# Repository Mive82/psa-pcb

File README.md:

# Important

**NOTE:** Unless you have access to a bunch of weird ICs used here, a way to solder 0201 and 0402 components,
and willpower to fix the defects listed below, don't bother assemblying the v1.0 version of the PCB.

# Peugeot Infotainment Project PCB

This is a repository for the PCB used in the second revision of the Peugeot Infotainment Project.
For the first revision, see the v0.1 branch.

It used <https://github.com/morcibacsi/PSAVanCanBridgeHW> as a base for the VAN communication hardware.

For more information, check out <https://github.com/Mive82/psa-docs>

## About the board

Unlike the previous v0.1 revision, on the v1.0 revision everything is contained on the board:
- Dual buck converter chips: One for the ESP and other ICs on the board (Battery power) and one for the Raspberry Pi and display (VAN+).
  - 3.3V LDO for the ESP32 after the 5V buck converter. Allows for very low voltage on the 12V input down to about 4 volts and the ESP will still work.
- ESP32-WROOM module. The USB to UART converter is not inclued, but the extra pins for resetting and flashing the board are routed to the connector.
- TSS463C VAN driver. Connected with a level shifter to the ESP
- MCP2551 CAN transciever. The RX pin is also connected to the ESP to allow receving in software.
- DS3231 RTC Chip for keeping the time. Connected to the Pi.

## Connections

The board has three JST GH connectors:
- Car power and data (JST GH 6 pin)
  - 12V battery power
  - 12V Switched (+VAN) power
  - VAN DATA and DATAB lines
- Display power output (JST GH 4 pin)
  - Outputs 5V for an external display
  - Also routes I2C pins from the Pi if needed
- ESP programming (JST GH 6 pin)
  - UART TX, RX, RTS and DTR pins as well as GND.

# Board Defects

Being the first proper revision, there are a lot of defects. Luckily they can all be solved.

## ESP flashing issues

The `GPIO12` pin is used for SPI communication with the TSS463C. It is also used as a strapping pin for determining the voltage used
to access the onboard flash. This pin is floating, so the value will not always be correct. This will result in regular booting
and flashing issues.

**SOLUTION**: Burn eFuses with `esptool.py` to permanently set the voltage used. On the ESP32-WROOM module we used, the voltage was 3.3V [Implemented]

## ESP first boot issues

When first powering the board on, the ESP will always boot into flash mode. This is because of a capacitor on the `GPIO0` pin that was not needed: `C6`.

**SOLUTION**: Remove the `C6` capacitor. [Implemented]

## VAN TX not working

The transistor switches used for putting the MCP2551 in a low-power state and resetting the TSS are not designed correctly.
They don't reset the TSS, but the MCP2551 is always put in a low power state which prevents it from sending any CAN/VAN data.

**SOLUTION**: Remove both transistor switches and surrounding hardware (`Q6`, `R21`, `R1`, `Q5` and `C1`). [Implemented]
Pull pin `Rs` on the MCP2551 to GND with a 4.7k resistor. Note that, according the datasheet, this will increase power draw
by 9 or 10 mA. [Implemented]

## ESP32 VAN RX not working after VAN+ dissapears

This issue occured due to an oversight on level shifter pins. The VCC reference pin on one side is tied to the VAN+ regulator and will
dissapear when VAN+ dissapears.

**SOLUTION**: On chip U11 cut the trace connecting pin 11 (`VCC(B)`) and `+5V ignition`. then connect pin 11 to `+5V Car Battery`. [Implemented]
Best location would the one of the pads of `R21` which is be removed to fix the issue above this one. 

### High deep sleep power consumption

The board pulls about 35mA on 12V during deep sleep. This increases the more voltage increases.
Not yet sure what is causing this, but removing the pull resistors from the `MODE` pins on the buck regulators reduces it to about 12mA.

**PARTIAL SOLUTION**: Remove `R110` and `R118`. [Implemented]

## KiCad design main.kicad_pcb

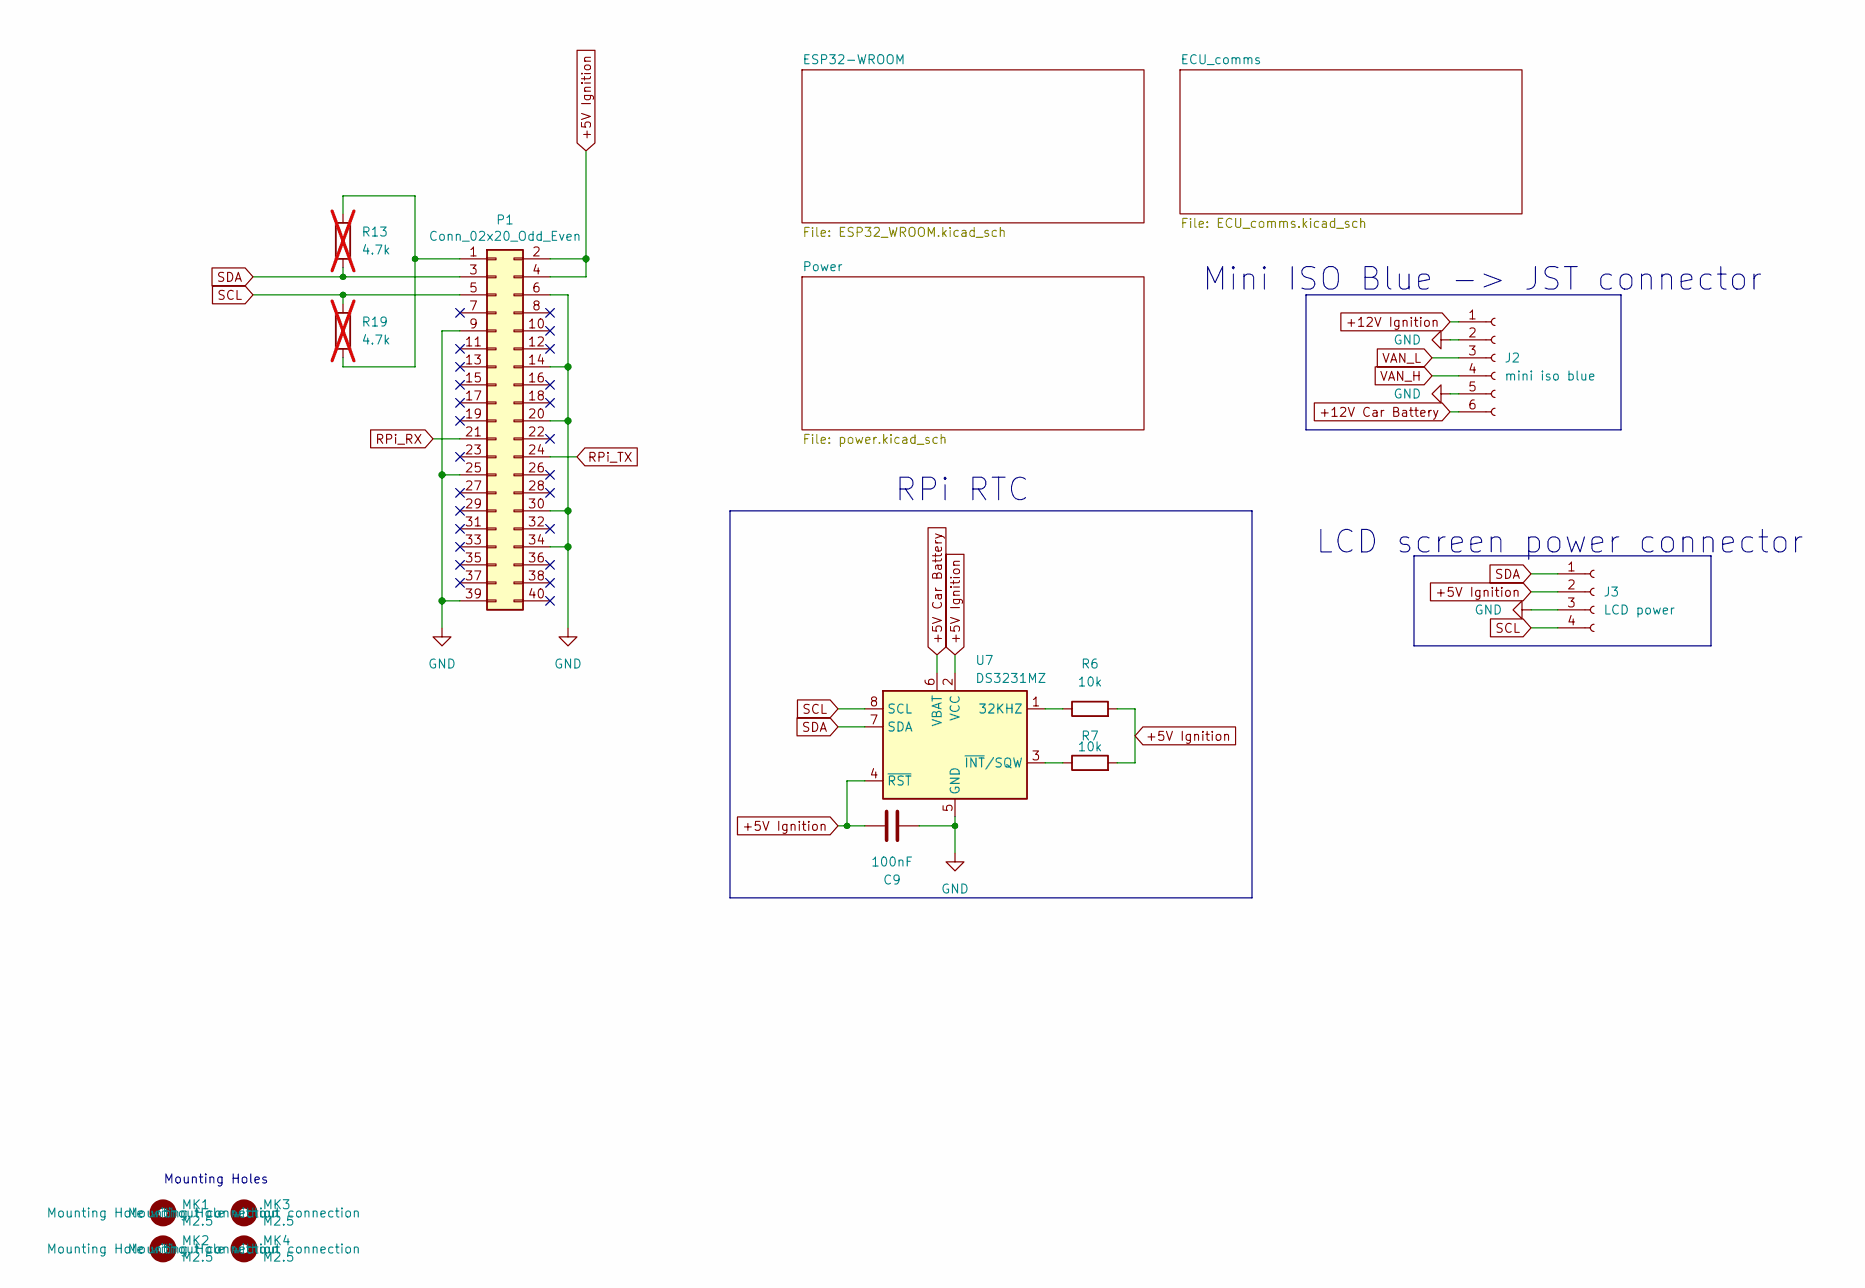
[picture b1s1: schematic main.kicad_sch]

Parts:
C9: 100nF; R_0805_2012Metric
J2: mini iso blue; JST_GH_SM06B-GHS-TB_1x06-1MP_P1.25mm_Horizontal
J3: LCD power; JST_GH_SM04B-GHS-TB_1x04-1MP_P1.25mm_Horizontal
MK1, MK2, MK3, MK4: M2.5; MountingHole_2.7mm_M2.5
P1: Conn_02x20_Odd_Even; PinSocket_2x20_P2.54mm_Vertical
R6, R7: 10k; R_0805_2012Metric
R13, R19: 4.7k; R_0402_1005Metric_Pad0.72x0.64mm_HandSolder; not fitted
U7: DS3231MZ; SOIC-8_3.9x4.9mm_P1.27mm

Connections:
+5V Car Battery: U7.6 (VBAT); also elsewhere on the board
+5V Ignition: C9.2, J3.2, P1.2, P1.4, R6.2, R7.2, U7.2 (VCC), U7.4 (~RST); also elsewhere on the board
+12V Car Battery: J2.6; also elsewhere on the board
+12V Ignition: J2.1; also elsewhere on the board
GND: C9.1, J2.2, J2.5, J3.3, P1.6, P1.9, P1.14, P1.20, P1.25, P1.30, P1.34, P1.39, U7.5 (GND); also elsewhere on the board
unnamed: P1.1, R13.1, R19.2
unnamed: R6.1, U7.1 (32KHZ)
unnamed: R7.1, U7.3 (~INT/SQW)
RPi_RX: P1.21; also elsewhere on the board
RPi_TX: P1.24; also elsewhere on the board
SCL: J3.4, P1.5, R19.1, U7.8 (SCL)
SDA: J3.1, P1.3, R13.2, U7.7 (SDA)
VAN_H: J2.4; also elsewhere on the board
VAN_L: J2.3; also elsewhere on the board

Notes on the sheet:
LCD screen power connector
Mini ISO Blue -> JST connector
Mounting Holes
RPi RTC

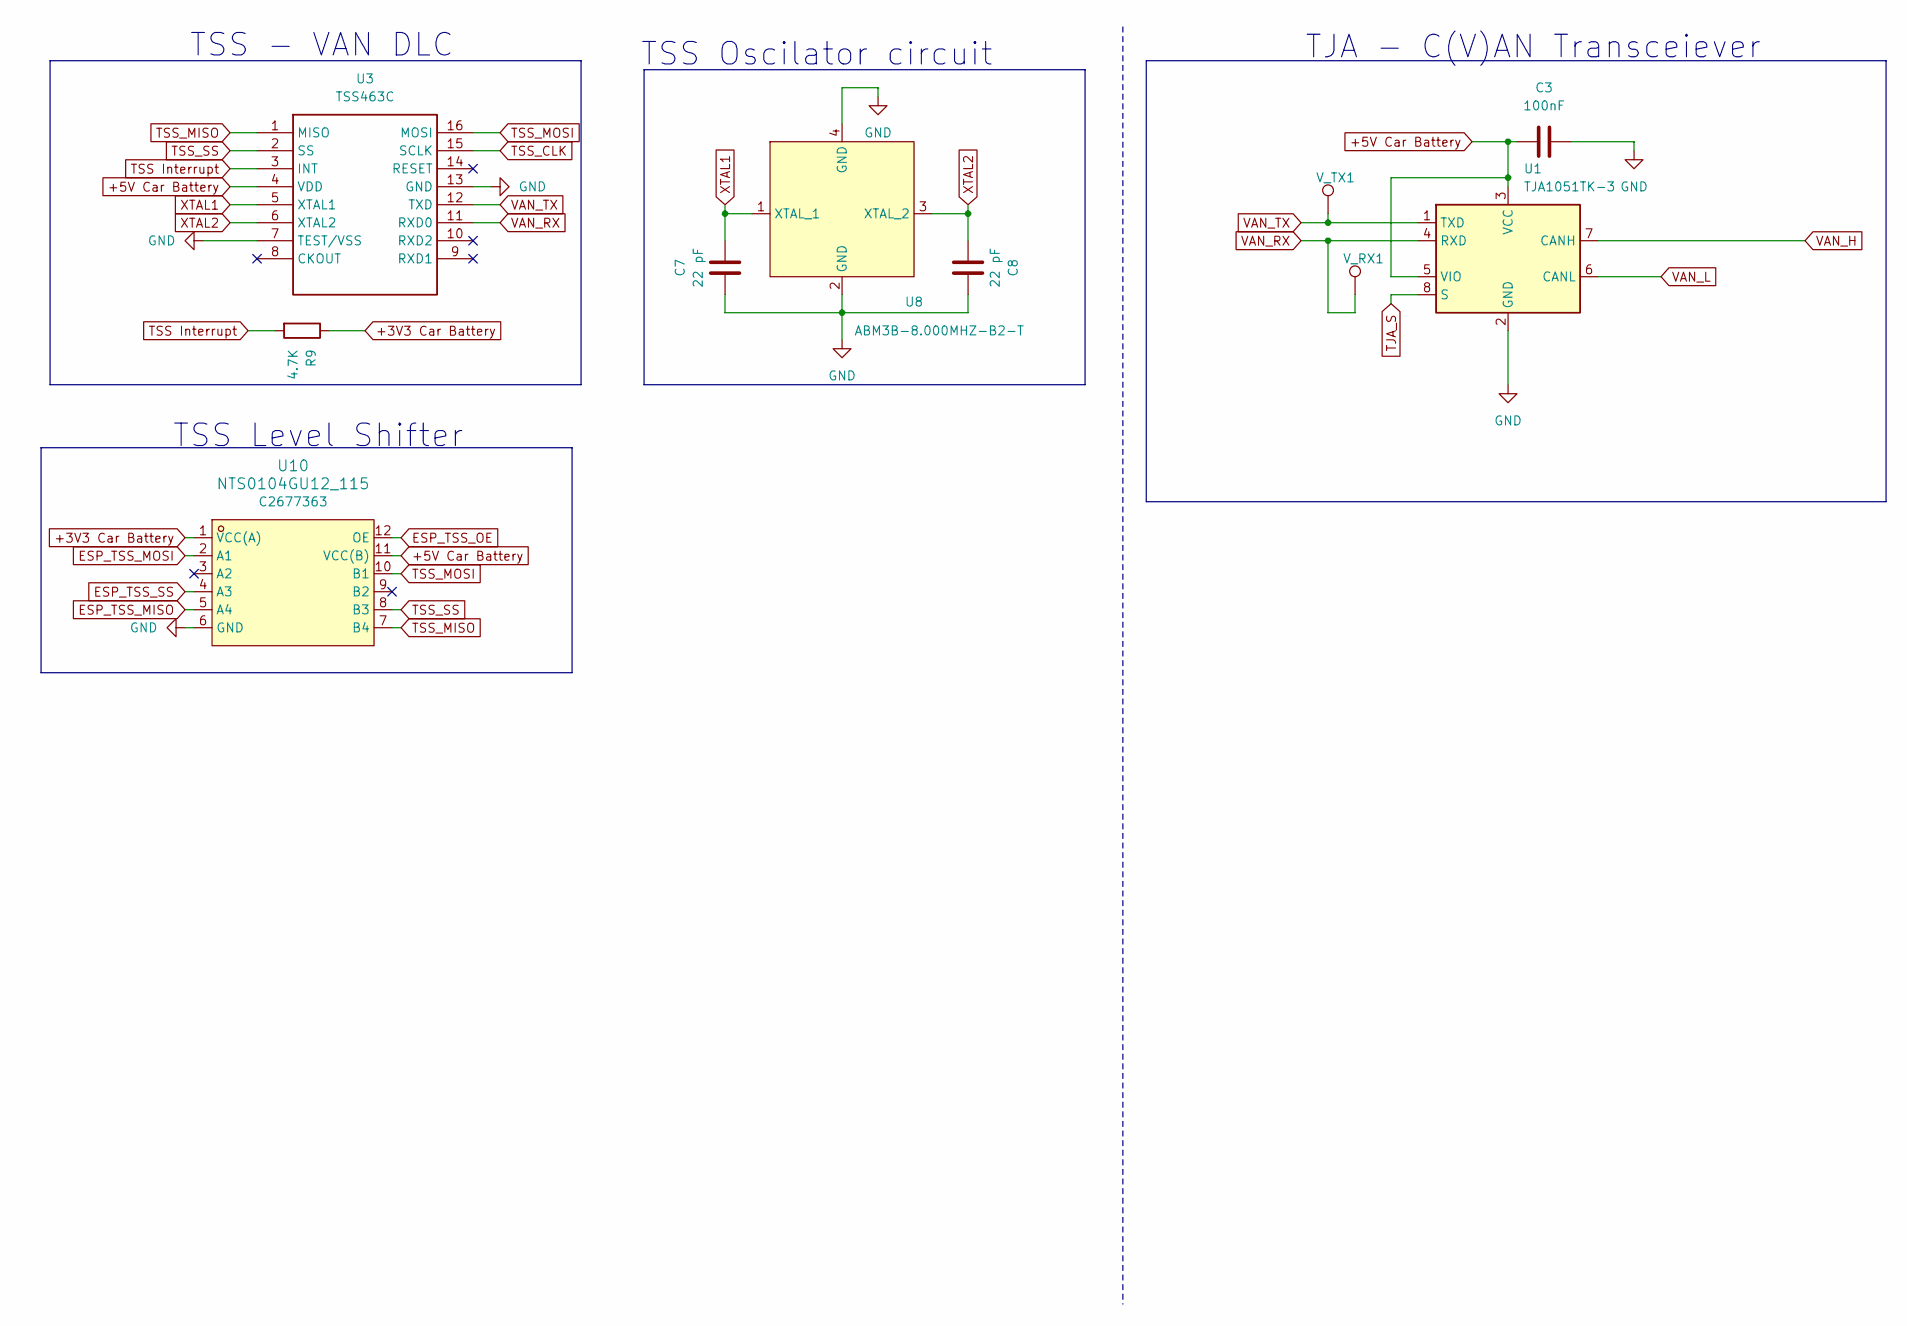
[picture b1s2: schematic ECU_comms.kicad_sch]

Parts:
C3: 100nF; C_0805_2012Metric
C7, C8: 22 pF; C_0805_2012Metric
R9: 4.7K; R_0805_2012Metric
U1: TJA1051TK-3; HVSON-8-1EP_3x3mm_P0.65mm_EP1.6x2.4mm
U3: TSS463C
U8: ABM3B-8.000MHZ-B2-T; Crystal_SMD_Abracon_ABM3B-4Pin_5.0x3.2mm
U10: NTS0104GU12_115; XQFN-12_L2.0-W1.7-P0.40-BL; LCSC Part C2677363
V_RX1: TestPoint; TestPoint_Pad_D1.0mm
V_TX1: TestPoint; TestPoint_Pad_D1.0mm

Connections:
+3V3 Car Battery: R9.1, U10.1 (VCC(A)); also elsewhere on the board
+5V Car Battery: C3.1, U1.3 (VCC), U1.5 (VIO), U3.4 (VDD), U10.11 (VCC(B)); also elsewhere on the board
ESP_TSS_MISO: U10.5 (A4); also elsewhere on the board
ESP_TSS_MOSI: U10.2 (A1); also elsewhere on the board
ESP_TSS_OE: U10.12 (OE); also elsewhere on the board
ESP_TSS_SS: U10.4 (A3); also elsewhere on the board
GND: C3.2, C7.1, C8.1, U1.2 (GND), U1.9 (GND), U3.7 (TEST/VSS), U3.13 (GND), U8.2 (GND), U8.4 (GND), U10.6 (GND); also elsewhere on the board
TJA_S: U1.8 (S); also elsewhere on the board
TSS Interrupt: R9.2, U3.3 (INT); also elsewhere on the board
TSS_CLK: U3.15 (SCLK); also elsewhere on the board
TSS_MISO: U3.1 (MISO), U10.7 (B4)
TSS_MOSI: U3.16 (MOSI), U10.10 (B1)
TSS_SS: U3.2 (SS), U10.8 (B3)
VAN_H: U1.7 (CANH); also elsewhere on the board
VAN_L: U1.6 (CANL); also elsewhere on the board
VAN_RX: U1.4 (RXD), U3.11 (RXD0), V_RX1.1; also elsewhere on the board
VAN_TX: U1.1 (TXD), U3.12 (TXD), V_TX1.1; also elsewhere on the board
XTAL1: C7.2, U3.5 (XTAL1), U8.1 (XTAL_1)
XTAL2: C8.2, U3.6 (XTAL2), U8.3 (XTAL_2)

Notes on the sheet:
TSS Oscilator circuit
TJA - C(V)AN Transceiever
TSS - VAN DLC
TSS Level Shifter

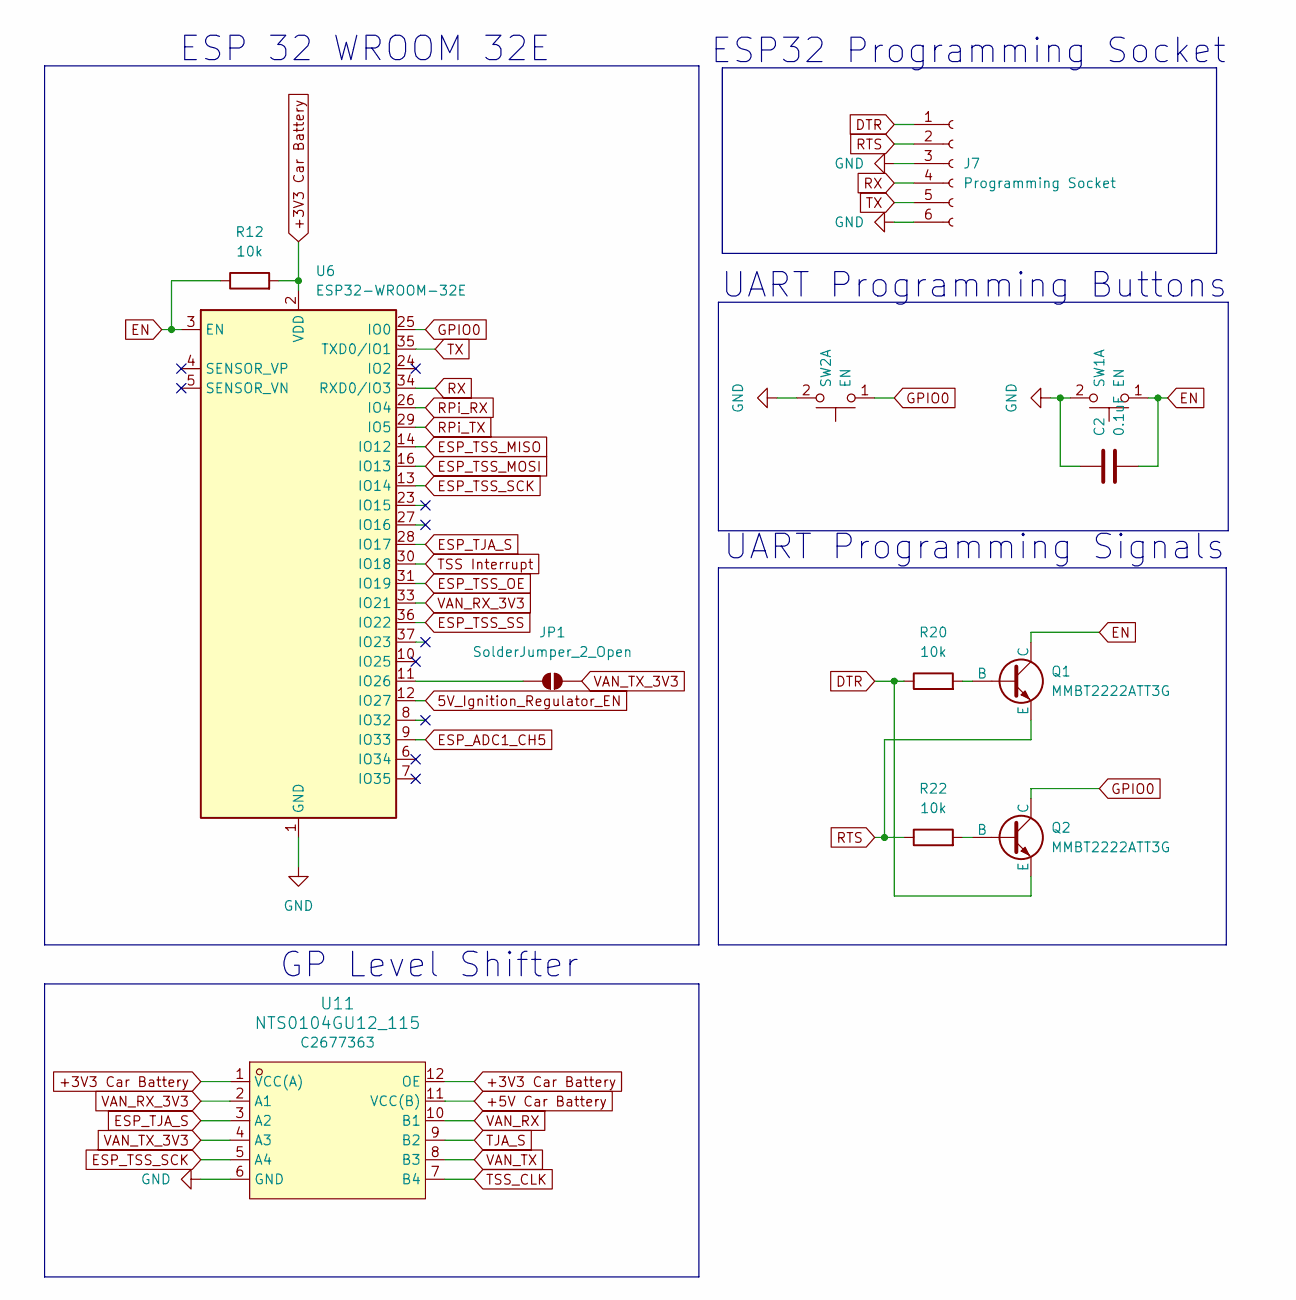
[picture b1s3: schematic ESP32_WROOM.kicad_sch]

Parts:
C2: 0.1uF; C_0805_2012Metric
J7: Programming Socket; JST_GH_BM06B-GHS-TBT_1x06-1MP_P1.25mm_Vertical
JP1: SolderJumper_2_Open; SolderJumper-2_P1.3mm_Open_Pad1.0x1.5mm
Q1, Q2: MMBT2222ATT3G; SOT-416
R12, R20, R22: 10k; R_0805_2012Metric
SW1, SW2: EN; SW_SPST_B3U-1000P-B
U6: ESP32-WROOM-32E; ESP32-WROOM-32D
U11: NTS0104GU12_115; XQFN-12_L2.0-W1.7-P0.40-BL; LCSC Part C2677363

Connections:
5V_Ignition_Regulator_EN: U6.12 (IO27); also elsewhere on the board
+3V3 Car Battery: R12.2, U6.2 (VDD), U11.1 (VCC(A)), U11.12 (OE); also elsewhere on the board
+5V Car Battery: U11.11 (VCC(B)); also elsewhere on the board
DTR: J7.1, Q2.3 (E), R20.1
EN: C2.2, Q1.1 (C), R12.1, SW1.1 (C), U6.3 (EN)
ESP_ADC1_CH5: U6.9 (IO33); also elsewhere on the board
ESP_TJA_S: U6.28 (IO17), U11.3 (A2)
ESP_TSS_MISO: U6.14 (IO12); also elsewhere on the board
ESP_TSS_MOSI: U6.16 (IO13); also elsewhere on the board
ESP_TSS_OE: U6.31 (IO19); also elsewhere on the board
ESP_TSS_SCK: U6.13 (IO14), U11.5 (A4)
ESP_TSS_SS: U6.36 (IO22); also elsewhere on the board
GND: C2.1, J7.3, J7.6, SW1.2 (D), SW2.2 (D), U6.1 (GND), U6.15 (GND), U6.38 (GND), U6.39 (GND), U11.6 (GND); also elsewhere on the board
GPIO0: Q2.1 (C), SW2.1 (C), U6.25 (IO0)
unnamed: JP1.1 (A), U6.11 (IO26)
unnamed: Q1.2 (B), R20.2
unnamed: Q2.2 (B), R22.2
RPi_RX: U6.26 (IO4); also elsewhere on the board
RPi_TX: U6.29 (IO5); also elsewhere on the board
RTS: J7.2, Q1.3 (E), R22.1
RX: J7.4, U6.34 (RXD0/IO3)
TJA_S: U11.9 (B2); also elsewhere on the board
TSS Interrupt: U6.30 (IO18); also elsewhere on the board
TSS_CLK: U11.7 (B4); also elsewhere on the board
TX: J7.5, U6.35 (TXD0/IO1)
VAN_RX: U11.10 (B1); also elsewhere on the board
VAN_RX_3V3: U6.33 (IO21), U11.2 (A1)
VAN_TX: U11.8 (B3); also elsewhere on the board
VAN_TX_3V3: JP1.2 (B), U11.4 (A3)

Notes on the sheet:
ESP 32 WROOM 32E
GP Level Shifter
ESP32 Programming Socket
UART Programming Signals
UART Programming Buttons

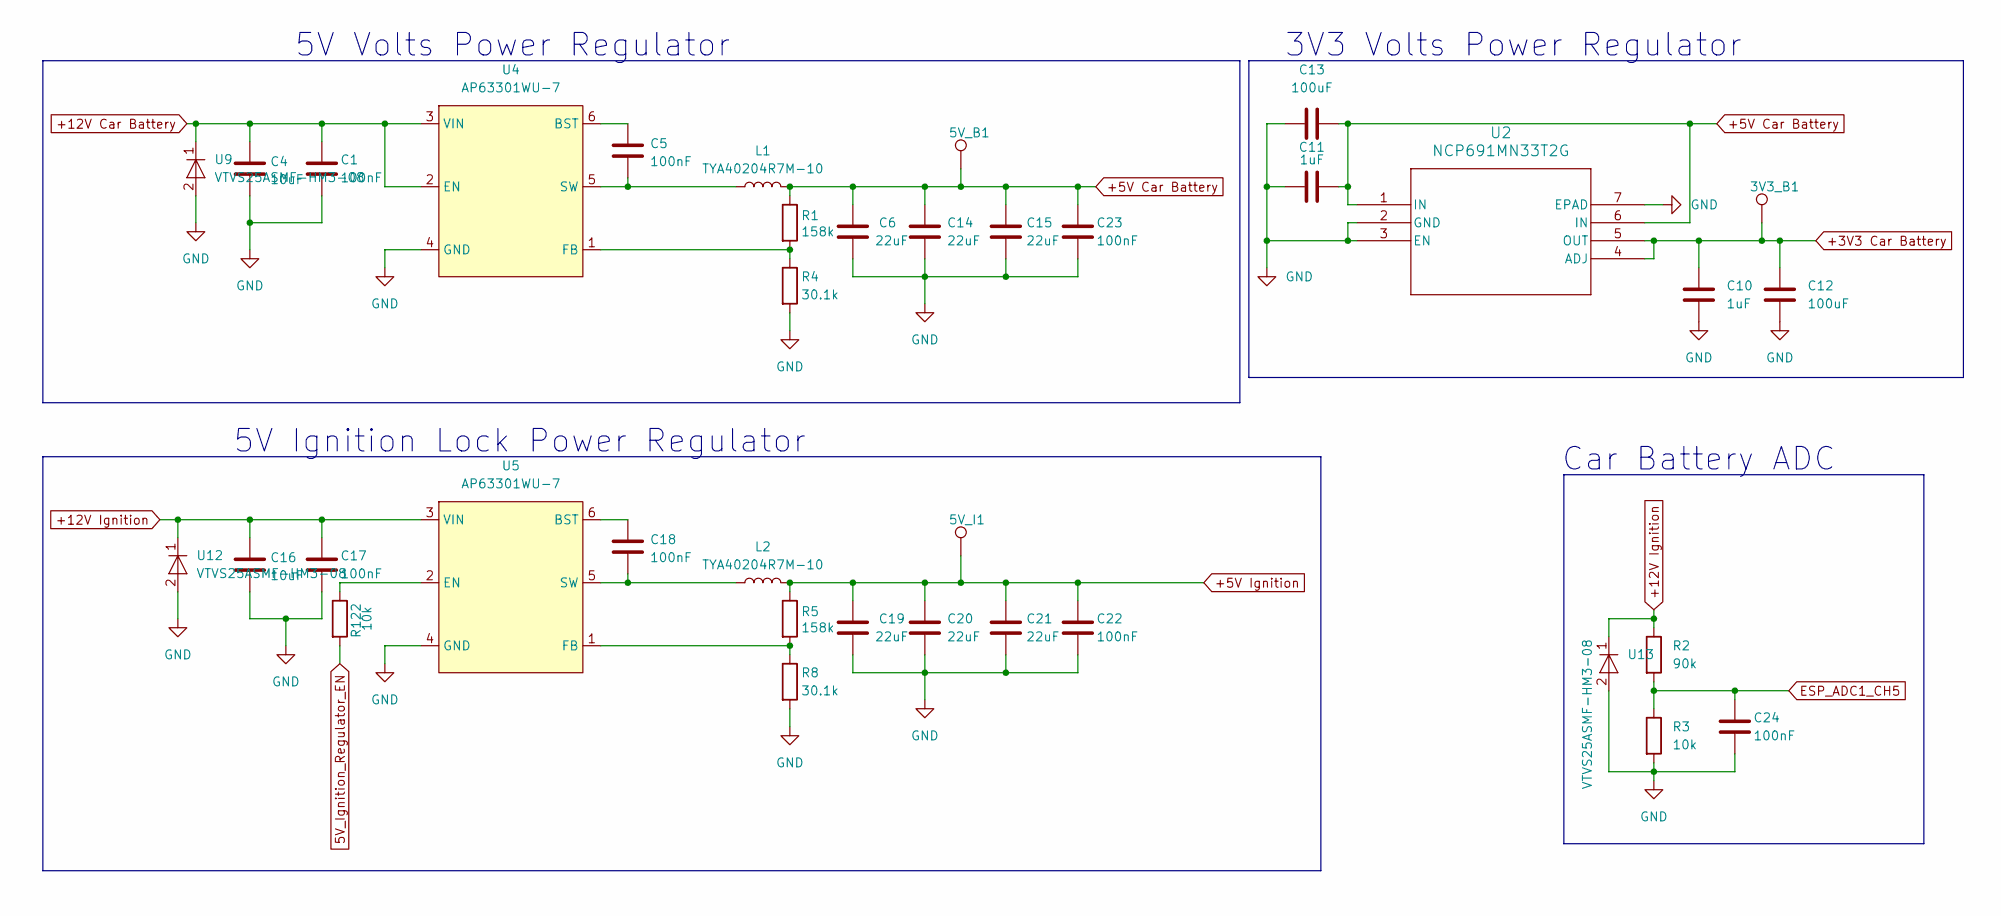
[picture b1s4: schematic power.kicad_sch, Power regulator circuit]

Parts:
3V3_B1, 5V_B1, 5V_I1: TestPoint; TestPoint_Pad_D1.0mm
C1, C5, C17, C18, C22, C23, C24: 100nF; C_0805_2012Metric
C4, C16: 10uF; C_0805_2012Metric
C6, C14, C15, C19, C20, C21: 22uF; C_0805_2012Metric
C10, C11: 1uF; C_0805_2012Metric
C12, C13: 100uF; C_0805_2012Metric
L1, L2: TYA40204R7M-10; IND_TYA40204_LRD
R1, R5: 158k; R_0805_2012Metric
R2: 90k; R_0805_2012Metric
R3, R122: 10k; R_0805_2012Metric
R4, R8: 30.1k; R_0805_2012Metric
U2: NCP691MN33T2G; DFN6_3X3_ONS
U4, U5: AP63301WU-7; TSOT-23-6
U9, U12, U13: VTVS25ASMF-HM3-08; D_SMF

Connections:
5V_Ignition_Regulator_EN: R122.2; also elsewhere on the board
+3V3 Car Battery: 3V3_B1.1, C10.1, C12.1, U2.4 (ADJ), U2.5 (OUT); also elsewhere on the board
+5V Car Battery: 5V_B1.1, C6.1, C11.2, C13.1, C14.1, C15.1, C23.1, L1.2, R1.1, U2.1 (IN), U2.6 (IN); also elsewhere on the board
+5V Ignition: 5V_I1.1, C19.1, C20.1, C21.1, C22.1, L2.2, R5.1; also elsewhere on the board
+12V Car Battery: C1.1, C4.1, U4.2 (EN), U4.3 (VIN), U9.1; also elsewhere on the board
+12V Ignition: C16.1, C17.1, R2.1, U5.3 (VIN), U12.1, U13.1; also elsewhere on the board
ESP_ADC1_CH5: C24.1, R2.2, R3.1; also elsewhere on the board
GND: C1.2, C4.2, C6.2, C10.2, C11.1, C12.2, C13.2, C14.2, C15.2, C16.2, C17.2, C19.2, C20.2, C21.2, C22.2, C23.2, C24.2, R3.2, R4.2, R8.2, U2.2 (GND), U2.3 (EN), U2.7 (EPAD), U4.4 (GND), U5.4 (GND), U9.2, U12.2, U13.2; also elsewhere on the board
unnamed: C5.1, U4.6 (BST)
unnamed: R1.2, R4.1, U4.1 (FB)
unnamed: C5.2, L1.1, U4.5 (SW)
unnamed: C18.1, U5.6 (BST)
unnamed: R122.1, U5.2 (EN)
unnamed: R5.2, R8.1, U5.1 (FB)
unnamed: C18.2, L2.1, U5.5 (SW)

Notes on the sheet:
5V Ignition Lock Power Regulator
Car Battery ADC
5V Volts Power Regulator
3V3 Volts Power Regulator

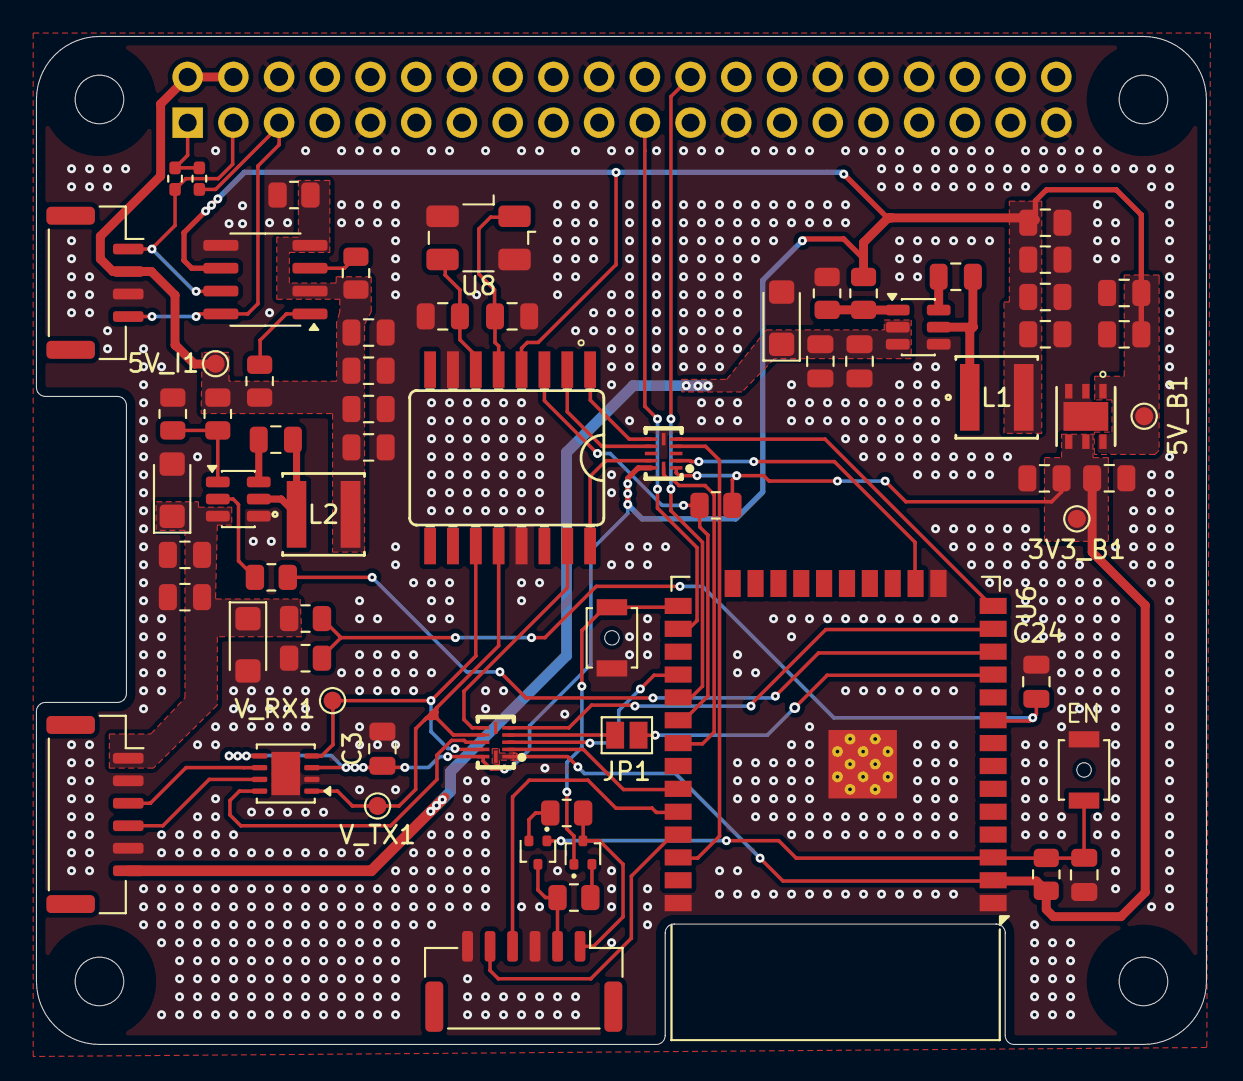
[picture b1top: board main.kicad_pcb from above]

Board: 2 copper layers, 65.0 x 56.0 mm, 72 parts (1 on the bottom side), 51 nets.

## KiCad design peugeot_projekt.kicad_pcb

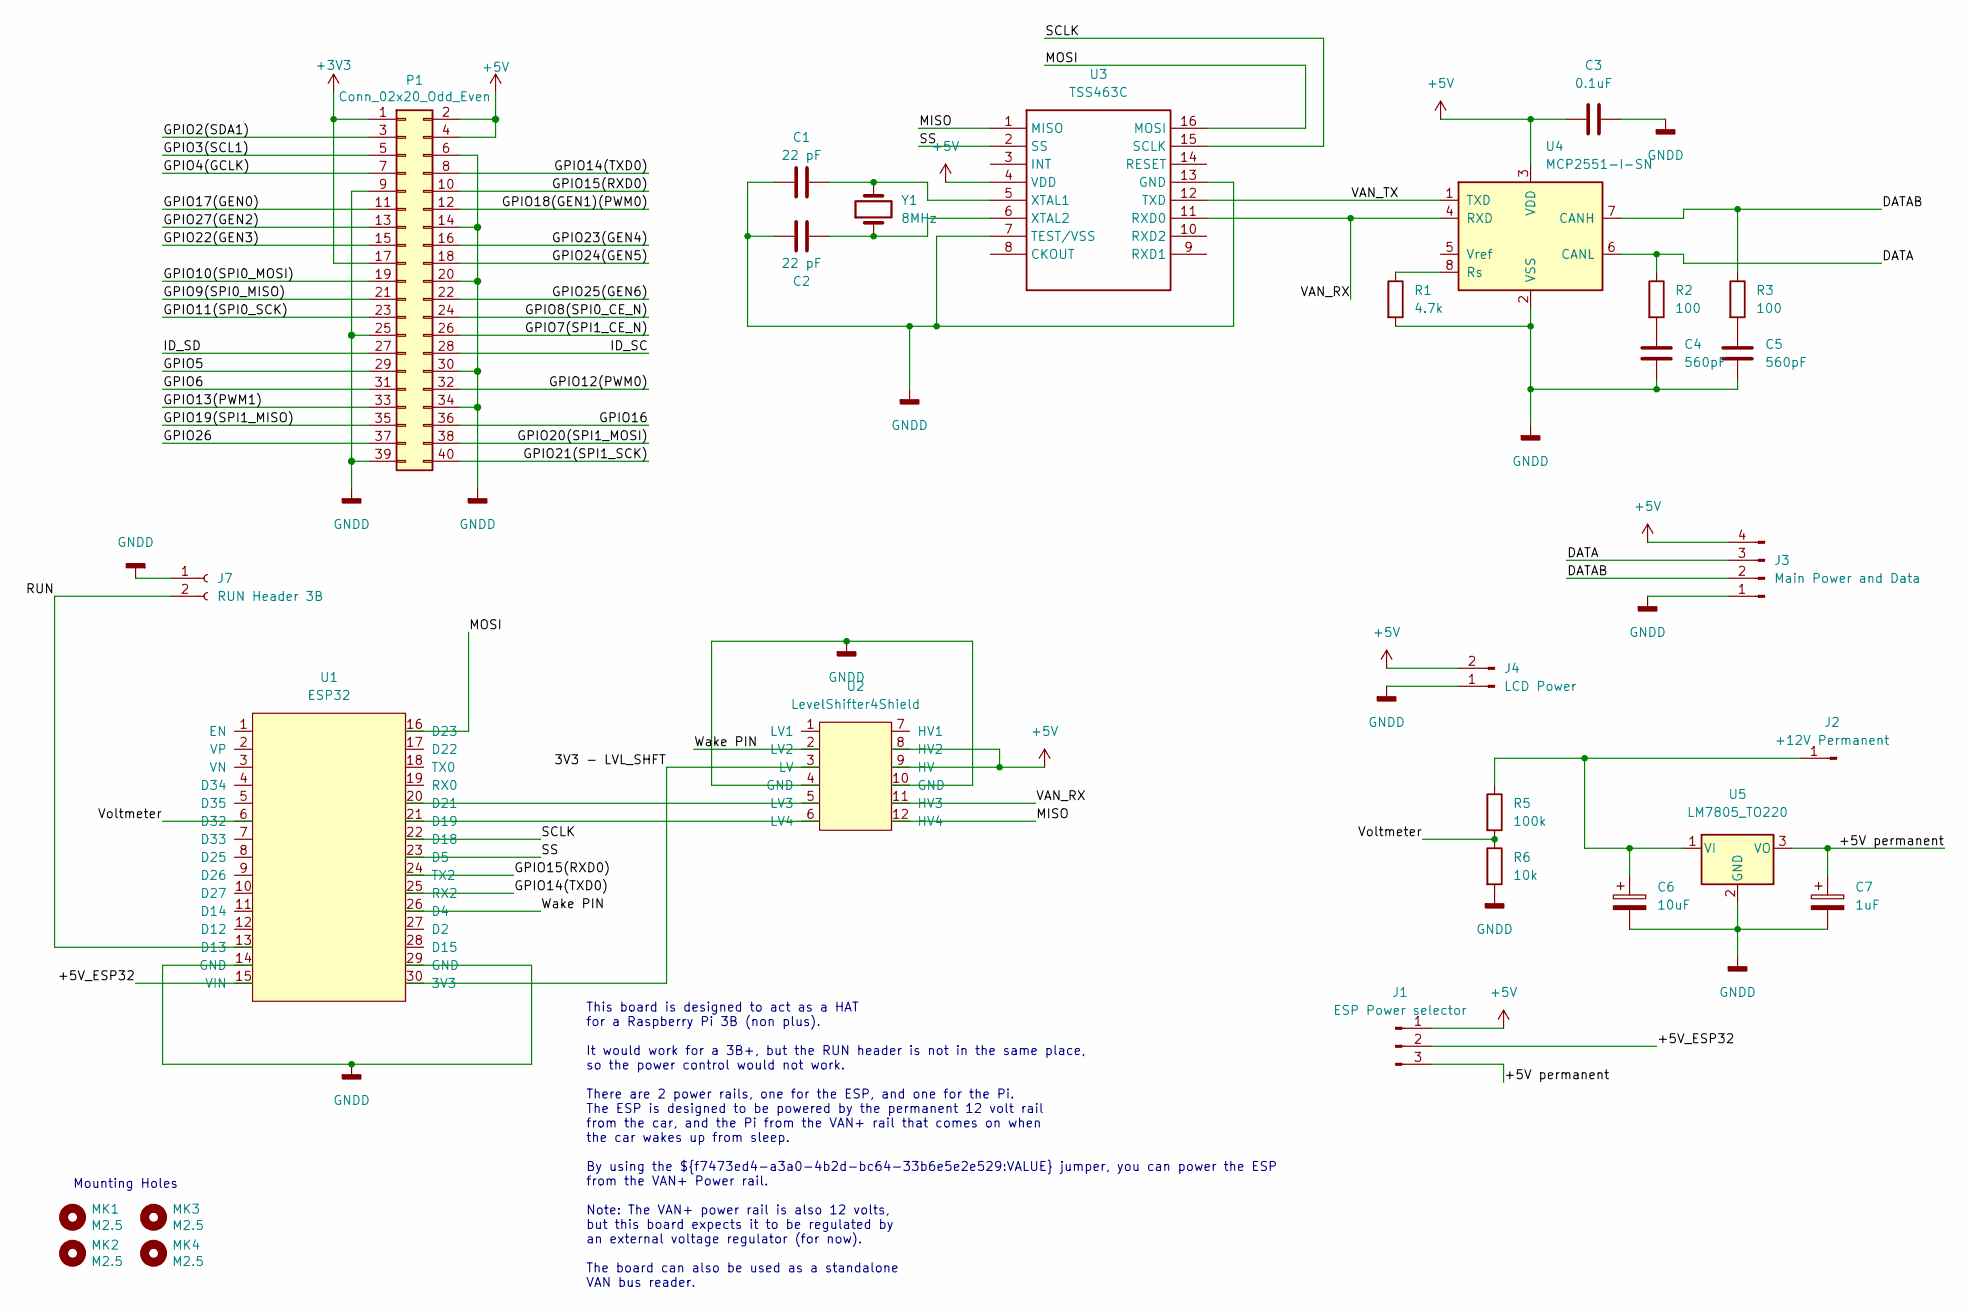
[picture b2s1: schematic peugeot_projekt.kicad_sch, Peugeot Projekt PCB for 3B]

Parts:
C1, C2: 22 pF; C_0603_1608Metric_Pad1.08x0.95mm_HandSolder
C3: 0.1uF; C_0603_1608Metric_Pad1.08x0.95mm_HandSolder
C4, C5: 560pF; C_0603_1608Metric_Pad1.08x0.95mm_HandSolder
C6: 10uF; C_0603_1608Metric_Pad1.08x0.95mm_HandSolder
C7: 1uF; C_0603_1608Metric_Pad1.08x0.95mm_HandSolder
J1: ESP Power selector; PinHeader_1x03_P2.54mm_Vertical
J2: +12V Permanent; PinHeader_1x01_P2.54mm_Vertical
J3: Main Power and Data; PinHeader_1x04_P2.54mm_Vertical
J4: LCD Power; PinHeader_1x02_P2.54mm_Vertical
J7: RUN Header 3B; PinSocket_1x02_P2.54mm_Vertical
MK1, MK2, MK3, MK4: M2.5; MountingHole_2.7mm_M2.5
P1: Conn_02x20_Odd_Even; PinSocket_2x20_P2.54mm_Vertical
R1: 4.7k; R_0603_1608Metric_Pad0.98x0.95mm_HandSolder
R2, R3: 100; R_0603_1608Metric_Pad0.98x0.95mm_HandSolder
R5: 100k; R_0603_1608Metric_Pad0.98x0.95mm_HandSolder
R6: 10k; R_0603_1608Metric_Pad0.98x0.95mm_HandSolder
U1: ESP32; ESP32_shield
U2: LevelShifter4Shield; LevelShifter4_shield
U3: TSS463C
U4: MCP2551-I-SN; SOIC-8_3.9x4.9mm_P1.27mm
U5: LM7805_TO220; TO-220-3_Vertical
Y1: 8MHz; Crystal_HC18-U_Vertical

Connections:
+3V3: P1.1, P1.17
+5V: C3.1, J1.1, J3.4, J4.2, P1.2, P1.4, U2.8 (HV2), U2.9 (HV), U3.4 (VDD), U4.3 (VDD)
/3V3 - LVL_SHFT: U1.30 (3V3), U2.3 (LV)
/+5V permanent: C7.1, J1.3, U5.3 (VO)
/+5V_ESP32: J1.2, U1.15 (VIN)
/DATA: J3.3, R2.1, U4.6 (CANL)
/DATAB: J3.2, R3.1, U4.7 (CANH)
/GPIO2(SDA1): P1.3
/GPIO3(SCL1): P1.5
/GPIO4(GCLK): P1.7
/GPIO5: P1.29
/GPIO6: P1.31
/GPIO7(SPI1_CE_N): P1.26
/GPIO8(SPI0_CE_N): P1.24
/GPIO9(SPI0_MISO): P1.21
/GPIO10(SPI0_MOSI): P1.19
/GPIO11(SPI0_SCK): P1.23
/GPIO12(PWM0): P1.32
/GPIO13(PWM1): P1.33
/GPIO14(TXD0): P1.8, U1.25 (RX2)
/GPIO15(RXD0): P1.10, U1.24 (TX2)
/GPIO16: P1.36
/GPIO17(GEN0): P1.11
/GPIO18(GEN1)(PWM0): P1.12
/GPIO19(SPI1_MISO): P1.35
/GPIO20(SPI1_MOSI): P1.38
/GPIO21(SPI1_SCK): P1.40
/GPIO22(GEN3): P1.15
/GPIO23(GEN4): P1.16
/GPIO24(GEN5): P1.18
/GPIO25(GEN6): P1.22
/GPIO26: P1.37
/GPIO27(GEN2): P1.13
/ID_SC: P1.28
/ID_SD: P1.27
/MISO: U2.12 (HV4), U3.1 (MISO)
/MOSI: U1.16 (D23), U3.16 (MOSI)
/RUN: J7.2, U1.13 (D13)
/SCLK: U1.22 (D18), U3.15 (SCLK)
/SS: U1.23 (D5), U3.2 (SS)
/VAN_RX: U2.11 (HV3), U3.11 (RXD0), U4.4 (RXD)
/VAN_TX: U3.12 (TXD), U4.1 (TXD)
/Voltmeter: R5.2, R6.1, U1.6 (D32)
/Wake PIN: U1.26 (D4), U2.2 (LV2)
GNDD: C1.1, C2.1, C3.2, C4.1, C5.1, C6.2, C7.2, J3.1, J4.1, J7.1, P1.6, P1.9, P1.14, P1.20, P1.25, P1.30, P1.34, P1.39, R1.2, R6.2, U1.14 (GND), U1.29 (GND), U2.4 (GND), U2.10 (GND), U3.7 (TEST/VSS), U3.13 (GND), U4.2 (VSS), U5.2 (GND)
unnamed: C1.2, U3.5 (XTAL1), Y1.2
unnamed: C2.2, U3.6 (XTAL2), Y1.1
unnamed: C4.2, R2.2
unnamed: C5.2, R3.2
unnamed: C6.1, J2.1, R5.1, U5.1 (VI)
unnamed: R1.1, U4.8 (Rs)
unnamed: U1.20 (D21), U2.5 (LV3)
unnamed: U1.21 (D19), U2.6 (LV4)

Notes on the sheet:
This board is designed to act as a HAT for a Raspberry Pi 3B (non plus). It would work for a 3B+, but the RUN header is not in the same place, so the power control would not work. There are 2 power rails, one for the ESP, and one for the Pi. The ESP is designed to be powered by the permanent 12 vol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
Mounting Holes

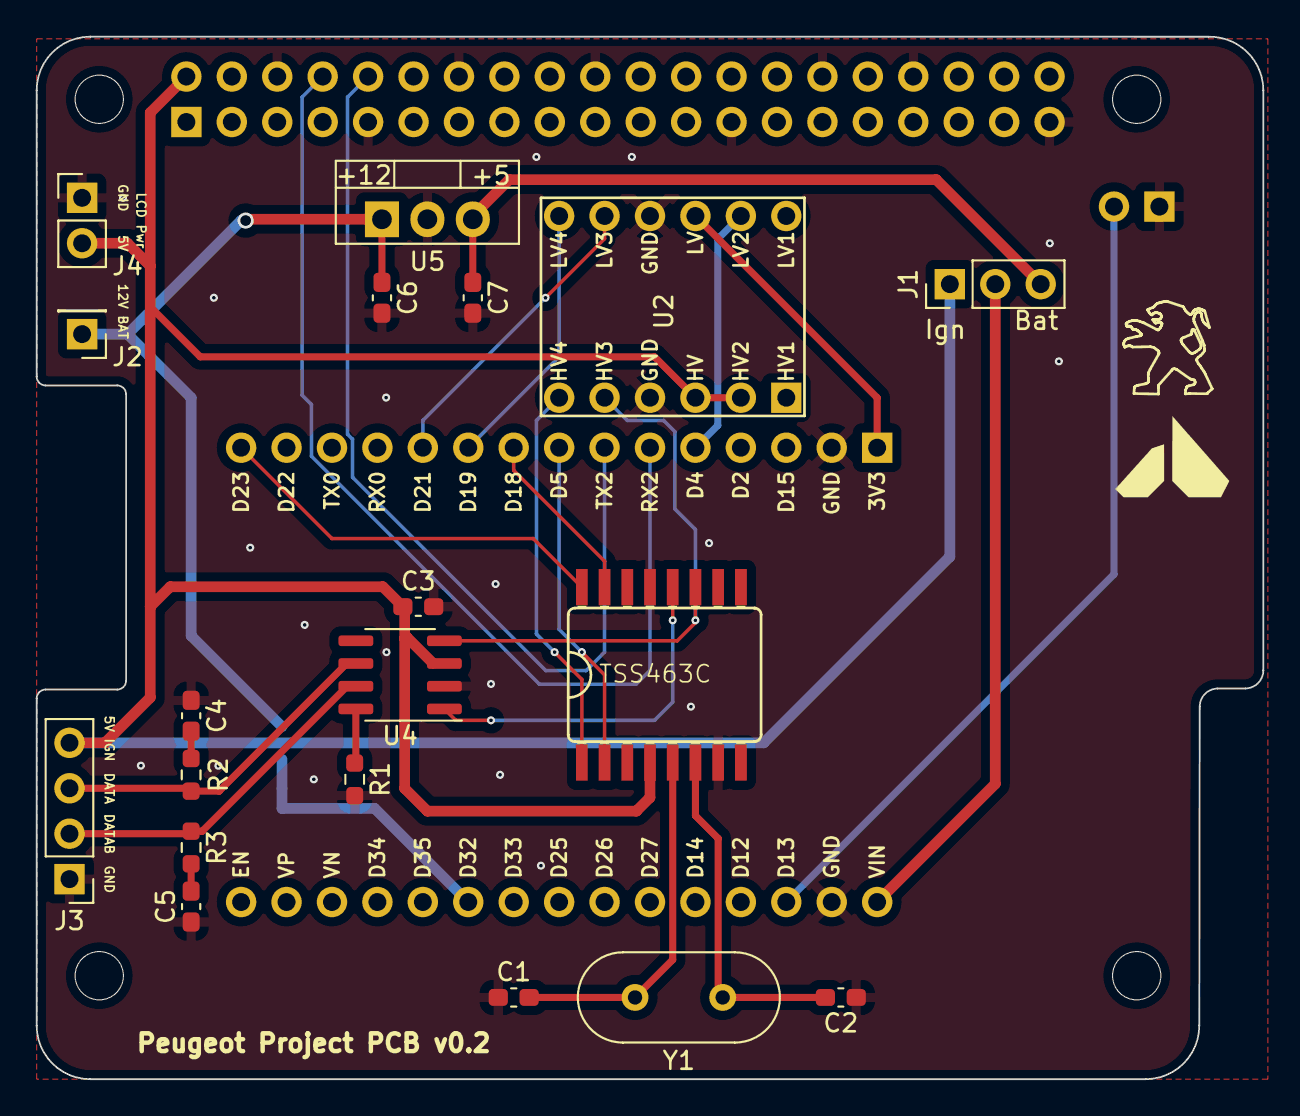
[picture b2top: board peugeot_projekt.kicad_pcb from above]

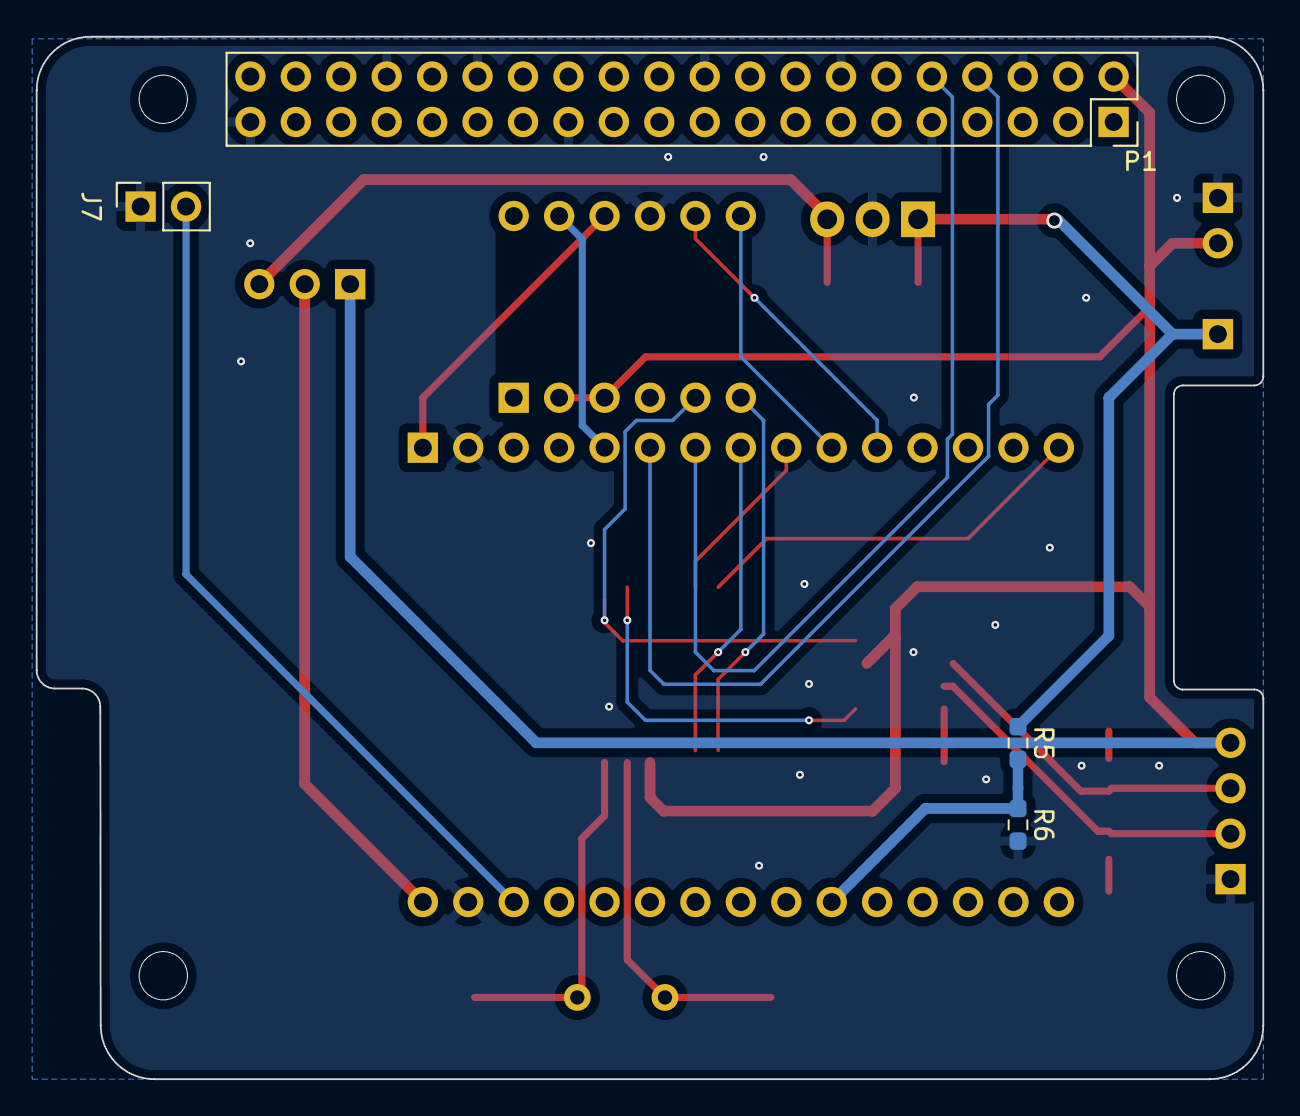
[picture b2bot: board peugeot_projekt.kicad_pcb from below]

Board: 2 copper layers, 68.6 x 58.3 mm, 28 parts (4 on the bottom side), 27 nets.

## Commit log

2022-09-16 Progress on v0.2 of the board
2022-09-16 Fix bom
2025-03-25 changed repo structure
2025-10-01 v1.0 - Second revision of the PCB
2025-10-17 implemented the changes from 'Board defects'
2025-11-03 2 layer PCB
2026-02-14 changed the CAN transceiever; fixed the transiever typo
2026-02-17 added direct VAN_TX to ESP connection
2026-02-18 changed power regulators, updated PCB
2026-02-19 added 3D models; light touch-ups
2026-02-19 removed temp file OUTPUT
2026-02-20 switched to vertial program connector, changed logo position
2026-02-20 fixing a fuckup
2026-03-13 added tvs diodes, 100nF, pull-up for TSS interrupt
2026-03-15 Modified ADC resistors. Added bypass cap to ADC.
    Removed some ground islands.
    Removed lock files and added them to gitignore.
2026-04-30 Change inductor type.
2026-04-30 Update bom values with actual chip names
